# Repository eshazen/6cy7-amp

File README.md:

# 6CY7-amp

This is a low power single-ended tridode (SET) hi-fi amp for the
workshop.  It is essentially a build of the Cascade Tubes "Zebrawood"
amp: https://www.cascadetubes.com/the-6cy7-v2-0-zebrawood-amp/.  I'm
using transformers from MusicalPowerSupplies.com.

PCB design here is 388 x 194mm.  It's the standard 1oz copper, 1.6mm thick.
Everything is on the PCB.  Mounted on a wooden base on 3/4 inch standoffs (including standoffs under the PT).  Case is 20mm 80/20 T-slot rail with acrylic side panels.  Complete overkill, but I like the industrial look!

<table>
  <tr><td>
    
  <tr><td>

  <td>

</table>

## Want to build one?

See https://github.com/eshazen/6cy7-amp/blob/main/BuildNotes.md

## News

**2021-02-20**

Working on a second PCB.  MPS has a long lead time on the PT.  
Ordered two OT8SE OTs and one of these:  AS-1T175 -- (2x 175V @ 280mA, 2x 6.3V @ 3A).
This thing is toroidal, 3.9" dia, 2" h.  Plan to mount it vertically on a bracket above the PCB.

**2021-01-15**

It's done!  Sounds great!  A couple of concerns:

I forgot the R/C filter for the preamp stage B+.  No audible defects due to this, but if someone else wants
to consider using this PCB design the R+C should be added.

One of the "NOS" 6CY7s (a Tung-Sol, made in USA) ran very hot (right at 32mA, 5.4W plate diss.) with
the 1k cathode resistor.  Swapped it for another of indeterminate make and it is fine.  Both channels
now around 27mA (4.6W).

**2021-01-03**

* 2/29/20: Iron ordered from MusicalPowerSupplies.com for a ~ 1/15/21 ship date
* 1/2/21: Parts ordered from DigiKey and Antique Electronic Supply
* 1/3/21: PCBs ordered from JLC (white soldermask, black silkscreen, cool, eh?)

Total spent with some spare stuff thrown in ~ US $350.00.  Hope to have it running by end of January!

**Speakers** Need some small bookshelf speakers to go with it.  Will test the amp with what I have lying around before making any decisions.  The easiest would be to buy another pair of Minimus-7's and apply the 'Zilch' crossover mod.

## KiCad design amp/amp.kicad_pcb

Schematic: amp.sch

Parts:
C1, C3: .0033uF; C_Axial_L17.0mm_D6.5mm_P20.00mm_Horizontal
C2, C4: 100uF; CP_Radial_D8.0mm_P3.50mm
C5: 5nF 400V Y4; C_Disc_D11.0mm_W5.0mm_P10.00mm
C6: 33uF; CP_Radial_D12.5mm_P5.00mm
C7, C8, C9: 100uF 350V; CP_Radial_D18.0mm_P7.50mm
F1: Fuse; HBH-I-R
H1, H2, H3, H4, H5, H6: MTG; MountingHole_6.4mm_M6_Pad
J1: Conn_01x05; GSP1.8101.1
J2: DUAL_RCA; PJRAS2X1S01AUX
L1: 5H/156L; 156L
L2, L3: 5H; 155H
LS1, LS2: Speaker; Keystone_4109
NE1: A1A
R1, R4, R6, R9: 1.5k; R_Axial_DIN0414_L11.9mm_D4.5mm_P15.24mm_Horizontal
R2, R7, R15: 100k; R_Axial_DIN0414_L11.9mm_D4.5mm_P15.24mm_Horizontal
R3, R8: 1M; R_Axial_DIN0414_L11.9mm_D4.5mm_P15.24mm_Horizontal
R5, R10: 1k 1W; R_Axial_DIN0414_L11.9mm_D4.5mm_P15.24mm_Horizontal
R11, R12, R13, R14: 100; R_Axial_DIN0414_L11.9mm_D4.5mm_P15.24mm_Horizontal
RV1, RV2: 100k_audio; P260P-D1BS3CA
SW1: SW_SPST_GND; 8GA1016-Z
T1, T2: Transformer_1P_1S; OT8SE
T3: Transformer_PT190.2; PT190_2
U1, U2: 6CY7; Valve_Noval_P
U3: 6CA4; Valve_Noval_P

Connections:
/L: F1.2, J1.1
Earth: C2.2, C4.2, C5.1, C6.2, C7.2, C8.2, C9.2, J2.2 (G1), J2.4 (G2), J2.5, J2.6, R1.2, R3.2, R5.2, R6.2, R8.2, R10.2, R11.2, R12.2, R13.2, R14.2, RV1.1, RV2.1, T3.5 (CT)
Earth_Protective: C5.2, H1.1, H2.1, H3.1, H4.1, H5.1, H6.1, J1.2, J1.4, J1.5, R11.1, SW1.4, SW1.5
HT: C8.1, L2.2, R2.1, T1.1
LINE: NE1.2, SW1.2, T3.3 (IN120V)
NEUT: J1.3, R15.2, T3.1 (IN0V)
unnamed: C1.1, R3.1, R4.2
unnamed: C1.2, R2.2, U1.6 (A)
unnamed: C2.1, R5.1, U1.9 (K)
unnamed: C3.1, R8.1, R9.2
unnamed: C3.2, R7.2, U2.6 (A)
unnamed: C4.1, R10.1, U2.9 (K)
unnamed: C6.1, L1.2, U3.3 (K)
unnamed: C7.1, L1.1, L2.1, L3.1
unnamed: F1.1, SW1.1
unnamed: J2.1 (S1), RV1.3
unnamed: J2.3 (S2), RV2.3
unnamed: LS1.1, T1.4
unnamed: LS1.2, T1.6
unnamed: LS2.1, T2.4
unnamed: LS2.2, T2.6
unnamed: NE1.1, R15.1
unnamed: R1.1, U1.8 (K)
unnamed: R4.1, U1.3 (G)
unnamed: R6.1, U2.8 (K)
unnamed: R9.1, U2.3 (G)
unnamed: R12.1, T3.12 (V2_6.3V), U1.4 (F1), U2.5 (F2)
unnamed: R13.1, T3.11 (F2_0V), U1.5 (F2), U2.4 (F1)
unnamed: R14.1, T3.8 (F1_0V), U3.5 (F2)
unnamed: RV1.2, U1.7 (G)
unnamed: RV2.2, U2.7 (G)
unnamed: T1.2, U1.1 (A)
unnamed: T2.2, U2.1 (A)
unnamed: T3.4 (PLT1), U3.7 (A2)
unnamed: T3.7 (PLT2), U3.1 (A1)
unnamed: T3.10 (F1_6.3V), U3.4 (F1)
VBUS: C9.1, L3.2, R7.1, T2.1

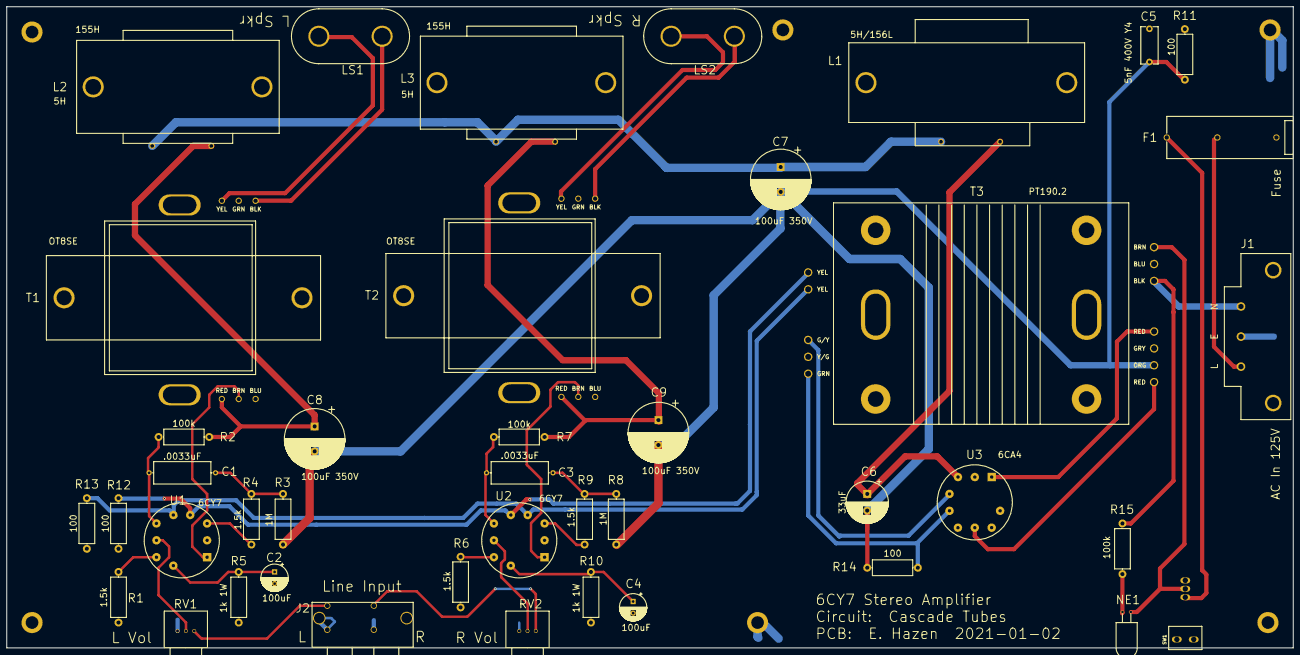
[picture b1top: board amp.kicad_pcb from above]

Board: 2 copper layers, 387.4 x 193.0 mm, 48 parts (0 on the bottom side), 37 nets.

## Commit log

2021-01-01 Working on PCB
2021-01-01 readme
2021-01-02 First try at placement
2021-01-02 save before branch
2021-01-02 First draft layout done
2021-01-02 Candidate for first build
2021-01-02 Change to 6-32 mounting holes
2021-01-03 Fix 156L footprint
2021-01-03 Rev A
2021-01-16 finished photos
2021-01-16 add photos, update readme
2021-01-16 start build notes
2021-01-26 bottom photo
2021-01-28 Fix 1.5K part number, add PDF schematic
2021-01-29 add final pix
2022-06-06 library updates
2022-06-06 Add 272HX symbol
2022-06-07 lib updates
2022-08-18 parts
2022-11-23 front panel mounting bracket
2022-11-28 3D printed side panel
